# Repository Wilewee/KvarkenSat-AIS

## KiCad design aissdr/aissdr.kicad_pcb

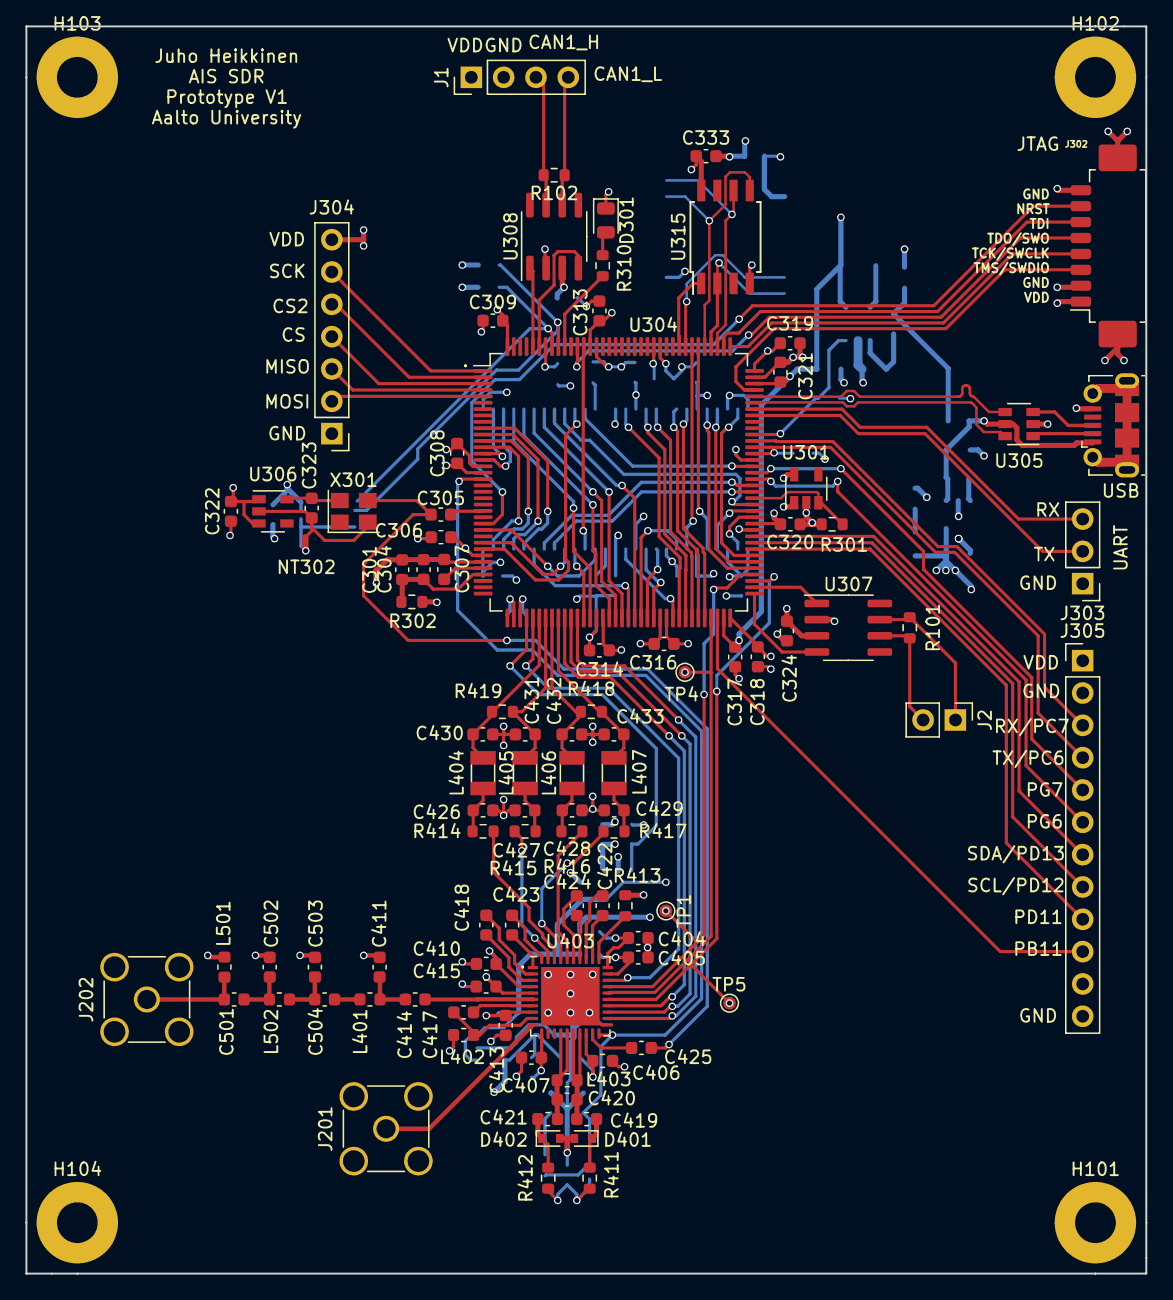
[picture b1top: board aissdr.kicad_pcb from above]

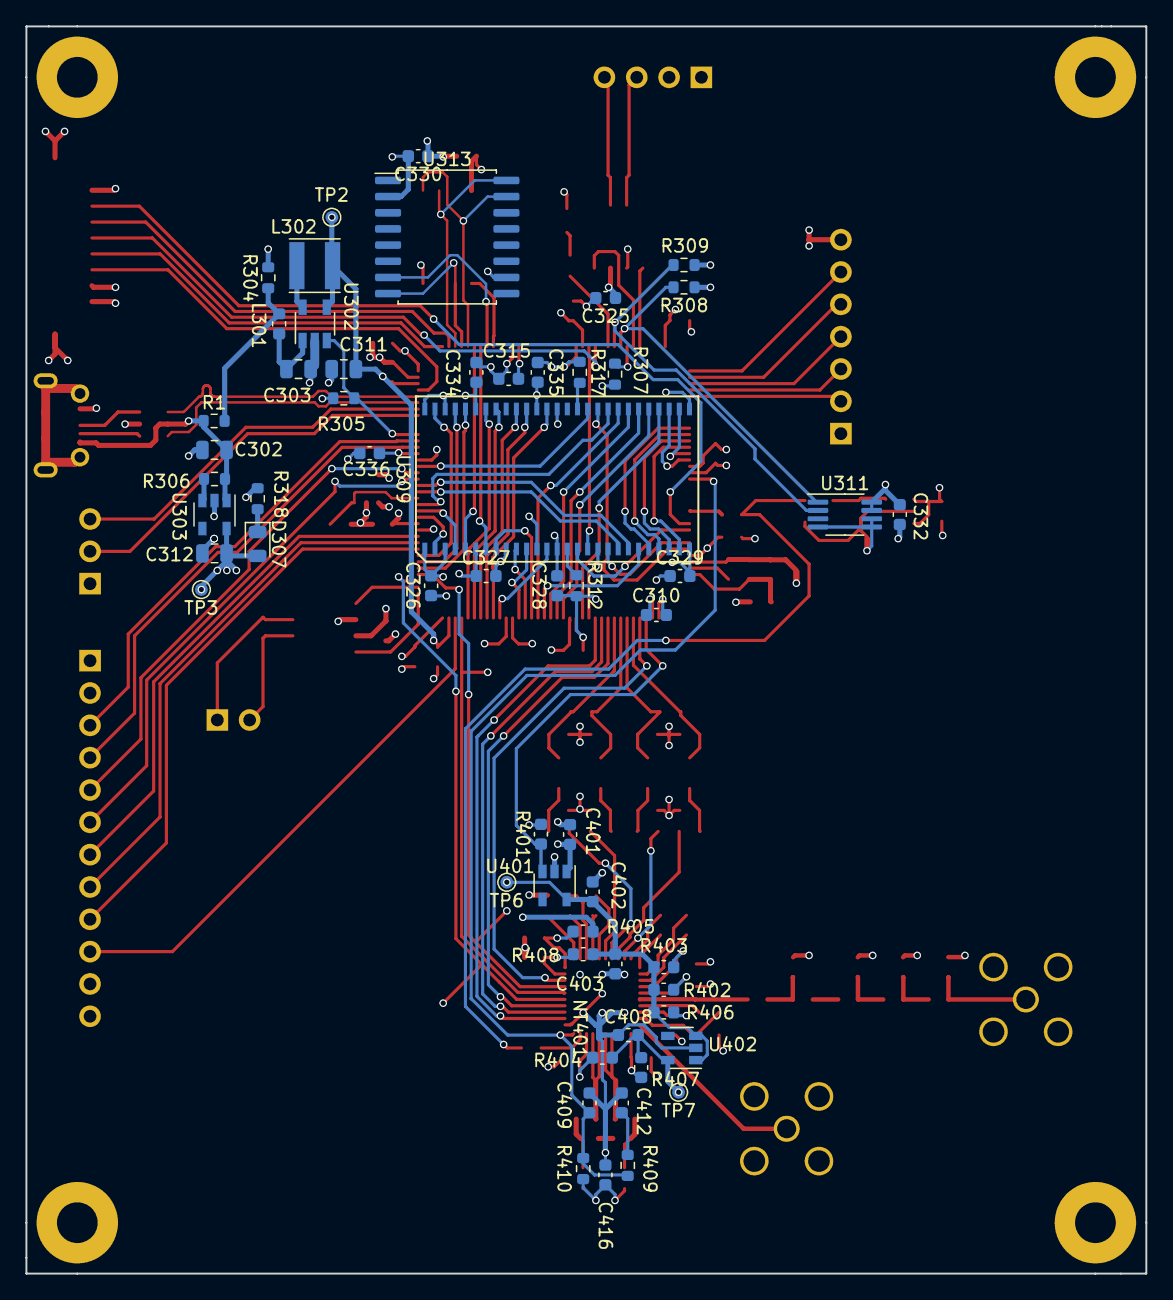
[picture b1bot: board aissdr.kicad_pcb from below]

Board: 4 copper layers, 88.0 x 98.0 mm, 160 parts (58 on the bottom side), 156 nets.

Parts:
C301, C307, C317, C321, C323, C402, C403, C408: 2u2; C_0603_1608Metric
C302: 2u2; C_0805_2012Metric
C303, C311, C312: 10u; C_0805_2012Metric
C304, C306, C308, C309, C310, C313, C314, C315, C316, C318, C319, C320, C322, C324, C325, C326, C327, C328, C329, C330, C332, C333, C334, C335, C336, C401, C404, C405: 100n; C_0603_1608Metric
C305, C414, C425: 1n; C_0603_1608Metric
C406, C407, C410, C413, C415: 10n; C_0603_1608Metric
C409, C412, C416: ?; C_0603_1608Metric
C411: 2p7; C_0603_1608Metric
C417: 18p; C_0603_1608Metric
C418, C422: 330p; C_0603_1608Metric
C419, C421: 47p; C_0603_1608Metric
C420: 0p; C_0603_1608Metric
C423, C424: 80p; C_0603_1608Metric
C426, C427, C428, C429, C430, C431, C432, C433: 3n3; C_0603_1608Metric
C501, C502: 10p; C_0603_1608Metric
C503: 12p; C_0603_1608Metric
C504: 100p; C_0603_1608Metric
D301: green; LED_0805_2012Metric
D307: red; LED_0805_2012Metric
D401, D402: SMV1234-079LF; D_SOD-523
H101, H102, H103, H104: MountingHole_Pad; MountingHole_3.2mm_M3_Pad
J1: Conn_01x07; PinHeader_1x04_P2.54mm_Vertical
J2: Conn_01x02; PinHeader_1x02_P2.54mm_Vertical
J201, J202: MCX right angle; SMA_Amphenol_901-144_Vertical
J301: USB_B_Micro; USB_Micro-B_Molex-105017-0001
J302: Molex_PicoBlade_53261-0871_1x08-1MP_P1.25mm_Horizontal
J303: PinHeader_1x03_P2.54mm_Vertical
J304: PinHeader_1x07_P2.54mm_Vertical
J305: PinHeader_1x12_P2.54mm_Vertical
L301: TBD; L_0603_1608Metric
L302: 2u2; L_Taiyo-Yuden_MD-4040
L401, L402: 150n; L_0603_1608Metric
L403: PCB inductor; L_0603_1608Metric
L404, L405, L406, L407: 470u; L_1007_2518Metric
L501: 27n; L_0603_1608Metric
L502: 15n; L_0603_1608Metric
NT301: VSSA; NetTie-2_SMD_Pad0.5mm
NT302: GNDXO; NetTie-2_SMD_Pad0.5mm
NT401: Net-Tie_2; NetTie-2_SMD_Pad0.5mm
R1, R304, R312, R317: 0; R_0603_1608Metric
R101, R102, R310, R318, R418, R419: 1k; R_0603_1608Metric
R301, R305, R306, R307: 470k; R_0603_1608Metric
R302: 10; R_0603_1608Metric
R308, R309, R411, R412, R413: 10k; R_0603_1608Metric
R401: 470k; C_0603_1608Metric
R402, R403, R406, R407: 3.3; C_0603_1608Metric
R404, R405, R408: 10; C_0603_1608Metric
R409, R410: ?; R_0603_1608Metric
R414, R415, R416, R417: 180; R_0603_1608Metric
TP1, TP2, TP3, TP4, TP5, TP6, TP7: TestPoint; TestPoint_Pad_D1.0mm
U301: MIC2091; SOT-23-5
U302: TPS62242-Q1; TSOT-23-5
U303: LP5907QMFX-3.3Q1; SOT-23-5
U304: STM32H743ZI; LQFP-144_20x20mm_P0.5mm
U305: USBLC6-2SC6; SOT-23-6
U306: LP5907MFX-3.0Q1; SOT-23-5
U307, U308: TCAN334; SOIC-8_3.9x4.9mm_P1.27mm
U309: IS42VS16160J-75TLI; TSOP-54-II
U311: AT30TS74; MSOP-8_3x3mm_P0.65mm
U313: MT29F1G01A; SOIC-16W_7.5x10.3mm_P1.27mm
U315: CY15B104QSN; SOIJ-8_5.3x5.3mm_P1.27mm
U401: LP5907QMFX-3.0Q1; SOT-23-5
U402: LP5907QMFX-2.8Q1; SOT-23-5
U403: CMX994A; QFN-40-1EP_6x6mm_P0.5mm_EP4.6x4.6mm
X301: ECS-TXO-2520-33-100-AN-TR; Crystal_SMD_3225-4Pin_3.2x2.5mm

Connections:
/3V3_PL: C306.2, C308.2, C309.2, C310.2, C312.1, C313.2, C314.2, C315.2, C316.2, C318.2, C319.2, C320.2, C322.2, C324.1, C325.1, C330.2, C332.2, C333.1, C336.2, C401.1, D307.2, J1.1, J302.1, J304.7, J305.1, R302.2, R304.2, R308.1, R309.1, R405.2, TP3.1, U301.1, U303.5, U304.17, U304.30, U304.39, U304.52, U304.62, U304.72, U304.84, U304.95, U304.108, U304.121, U304.131, U304.144, U306.1, U306.3, U307.3, U308.3, U311.7, U311.8, U313.2, U315.8, U401.1
/CAN1_H: J1.3, R102.2, U308.7
/CAN1_L: J1.4, R102.1, U308.6
/CAN2_H: J2.1, R101.2, U307.7
/CAN2_L: J2.2, R101.1, U307.6
/Transceiver/Filter/RF_Antenna: C501.2, J202.1, L501.1
/Transceiver/Filter/RF_RX: C504.1, L401.1
/Transceiver/Microcontroller/5V_USB: C302.1, J301.1, R1.1, R306.1, U303.1, U305.5
/Transceiver/Microcontroller/ADC_I_N: C431.2, L405.2, R419.1, U304.43
/Transceiver/Microcontroller/ADC_I_P: C430.1, L404.2, R419.2, U304.42
/Transceiver/Microcontroller/ADC_Q_N: C433.2, L407.2, R418.1, U304.45
/Transceiver/Microcontroller/ADC_Q_P: C432.1, L406.2, R418.2, U304.44
/Transceiver/Microcontroller/BOOT0: R307.2, U304.138
/Transceiver/Microcontroller/DEMOD_RESET: U304.41, U403.28
/Transceiver/Microcontroller/DEMOD_RXEN: U304.47, U403.23
/Transceiver/Microcontroller/DEMOD_TXEN: U304.48, U403.22
/Transceiver/Microcontroller/EN_3V0_A: R401.1, U304.40, U401.3
/Transceiver/Microcontroller/EN_3V3_D: R306.2, U303.3
/Transceiver/Microcontroller/EN_RAM: R301.1, U301.3, U304.88
/Transceiver/Microcontroller/EN_VDDCORE: R305.1, U302.3, U304.98
/Transceiver/Microcontroller/FDCAN1_RX: U304.139, U308.4
/Transceiver/Microcontroller/FDCAN1_TX: U304.140, U308.1
/Transceiver/Microcontroller/FDCAN2_RX: U304.73, U307.4
/Transceiver/Microcontroller/FDCAN2_TX: U304.74, U307.1
/Transceiver/Microcontroller/FLASH_CS: U304.116, U313.7
/Transceiver/Microcontroller/FMC_A0: U304.10, U309.23
/Transceiver/Microcontroller/FMC_A1: U304.11, U309.24
/Transceiver/Microcontroller/FMC_A2: U304.12, U309.25
/Transceiver/Microcontroller/FMC_A3: U304.13, U309.26
/Transceiver/Microcontroller/FMC_A4: U304.14, U309.29
/Transceiver/Microcontroller/FMC_A5: U304.15, U309.30
/Transceiver/Microcontroller/FMC_A6: U304.50, U309.31
/Transceiver/Microcontroller/FMC_A7: U304.53, U309.32
/Transceiver/Microcontroller/FMC_A8: U304.54, U309.33
/Transceiver/Microcontroller/FMC_A9: U304.55, U309.34
/Transceiver/Microcontroller/FMC_A10: U304.56, U309.22
/Transceiver/Microcontroller/FMC_A11: U304.57, U309.35
/Transceiver/Microcontroller/FMC_A12: U304.87, U309.36
/Transceiver/Microcontroller/FMC_BA0: U304.89, U309.20
/Transceiver/Microcontroller/FMC_BA1: U304.90, U309.21
/Transceiver/Microcontroller/FMC_D0: U304.85, U309.2
/Transceiver/Microcontroller/FMC_D1: U304.86, U309.4
/Transceiver/Microcontroller/FMC_D2: U304.114, U309.5
/Transceiver/Microcontroller/FMC_D3: U304.115, U309.7
/Transceiver/Microcontroller/FMC_D4: U304.58, U309.8
/Transceiver/Microcontroller/FMC_D5: U304.59, U309.10
/Transceiver/Microcontroller/FMC_D6: U304.60, U309.11
/Transceiver/Microcontroller/FMC_D7: U304.63, U309.13
/Transceiver/Microcontroller/FMC_D8: U304.64, U309.42
/Transceiver/Microcontroller/FMC_D9: U304.65, U309.44
/Transceiver/Microcontroller/FMC_D10: U304.66, U309.45
/Transceiver/Microcontroller/FMC_D11: U304.67, U309.47
/Transceiver/Microcontroller/FMC_D12: U304.68, U309.48
/Transceiver/Microcontroller/FMC_D13: U304.77, U309.50
/Transceiver/Microcontroller/FMC_D14: U304.78, U309.51
/Transceiver/Microcontroller/FMC_D15: U304.79, U309.53
/Transceiver/Microcontroller/FMC_SDCKE0: U304.29, U309.37
/Transceiver/Microcontroller/FMC_SDCLK: U304.93, U309.38
/Transceiver/Microcontroller/FMC_SDNCAS: U304.132, U309.17
/Transceiver/Microcontroller/FMC_SDNE0: U304.28, U309.19
/Transceiver/Microcontroller/FMC_SDNRAS: U304.49, U309.18
/Transceiver/Microcontroller/FMC_SDNWE: U304.26, U309.16
/Transceiver/Microcontroller/FRAM_CS: U304.117, U315.1
/Transceiver/Microcontroller/FREF: C305.2, C425.1, X301.3
/Transceiver/Microcontroller/FREF_MCU: C305.1, U304.23
/Transceiver/Microcontroller/GNDXO: C323.1, NT302.1, U306.2, X301.2
/Transceiver/Microcontroller/I2C1_SCL: R309.2, U304.136, U311.2
/Transceiver/Microcontroller/I2C1_SDA: R308.2, U304.137, U311.1
/Transceiver/Microcontroller/I2C4_SCL: J305.8, U304.81
/Transceiver/Microcontroller/I2C4_SDA: J305.7, U304.82
/Transceiver/Microcontroller/JTCK_SWCLK: J302.4, U304.109
/Transceiver/Microcontroller/JTDI: J302.6, U304.110
/Transceiver/Microcontroller/JTDO_SWO: J302.5, U304.133
/Transceiver/Microcontroller/JTMS_SWDIO: J302.3, U304.105
/Transceiver/Microcontroller/LED1: R310.1, U304.135
/Transceiver/Microcontroller/NRST: J302.7, U304.25
/Transceiver/Microcontroller/PB11: J305.10, U304.70
/Transceiver/Microcontroller/PD11: J305.9, U304.80
/Transceiver/Microcontroller/PG6: J305.6, U304.91
/Transceiver/Microcontroller/PG7: J305.5, U304.92
/Transceiver/Microcontroller/R_SCK: TP4.1, U304.69, U403.26
/Transceiver/Microcontroller/SPI3_MISO: U304.112, U313.8, U315.2
/Transceiver/Microcontroller/SPI3_MOSI: U304.113, U313.15, U315.5
/Transceiver/Microcontroller/SPI3_SCK: U304.111, U313.16, U315.6
/Transceiver/Microcontroller/SPI4_CS: J304.4, U304.3
/Transceiver/Microcontroller/SPI4_CS2: J304.5, U304.2
/Transceiver/Microcontroller/SPI4_MISO: J304.3, U304.4
/Transceiver/Microcontroller/SPI4_MOSI: J304.2, U304.5
/Transceiver/Microcontroller/SPI4_SCK: J304.6, U304.1
/Transceiver/Microcontroller/USART1_RX: J303.3, U304.102
/Transceiver/Microcontroller/USART1_TX: J303.2, U304.101
/Transceiver/Microcontroller/USART6_RX: J305.3, U304.97
/Transceiver/Microcontroller/USART6_TX: J305.4, U304.96
/Transceiver/Microcontroller/USB_CONN_D+: J301.3, U305.3
/Transceiver/Microcontroller/USB_CONN_D-: J301.2, U305.1
/Transceiver/Microcontroller/USB_D+: U304.104, U305.4
/Transceiver/Microcontroller/USB_D-: U304.103, U305.6
/Transceiver/Microcontroller/VCO_CV: C409.2, R409.1, R410.1, U304.18, U403.20
/Transceiver/Microcontroller/VDDA: C301.2, C304.2, R302.1, U304.33
/Transceiver/Microcontroller/VDDCORE: C311.1, C317.1, C321.2, L302.1, TP2.1, U302.4, U304.71, U304.106
/Transceiver/Microcontroller/VDDRAM: C326.2, C327.2, C328.2, C329.2, C334.2, C335.2, U301.5, U309.1, U309.3, U309.9, U309.14, U309.27, U309.43, U309.49
/Transceiver/Microcontroller/VDDXO: C323.2, U306.5, X301.4
/Transceiver/Microcontroller/VREF+: C307.2, U304.32
/Transceiver/Microcontroller/VSSA: C301.1, C304.1, C307.1, NT301.1, U304.31
/Transceiver/Receiver/3V0_A: C402.1, C403.2, R402.2, R403.2, R406.2, R408.2, TP6.1, U401.5, U402.1, U402.3
/Transceiver/Receiver/CDATA: TP1.1, U304.76, U403.27
/Transceiver/Receiver/CMX_RXIN: R415.2, U403.39
/Transceiver/Receiver/CMX_RXIP: R414.2, U403.38
/Transceiver/Receiver/CMX_RXQN: R417.2, U403.37
/Transceiver/Receiver/CMX_RXQP: R416.2, U403.36
/Transceiver/Receiver/CSN: U304.46, U403.24
/Transceiver/Receiver/GNDOSC: C408.1, C409.1, C412.1, C416.1, D401.2, D402.2, NT401.1, U402.2
/Transceiver/Receiver/RDATA: TP5.1, U304.75, U403.25
/Transceiver/Receiver/RF_TXLO: J201.1, U403.10
/Transceiver/Receiver/VDDOSC: C408.2, R404.2, R407.2, TP7.1, U402.5
GND: C302.2, C303.2, C306.1, C308.1, C309.1, C310.1, C311.2, C312.2, C313.1, C314.1, C315.1, C316.1, C317.2, C318.1, C319.1, C320.1, C321.1, C322.1, C324.2, C325.2, C326.1, C327.1, C328.1, C329.1, C330.1, C332.1, C333.2, C334.1, C335.1, C336.1, C401.2, C402.2, C403.1, C404.1, C405.1, C406.1, C407.1, C410.1, C411.1, C413.1, C415.1, C426.2, C427.1, C428.2, C429.1, C430.2, C431.1, C432.2, C433.1, C502.1, C503.1, D301.1, J1.2, J201.2, J202.2, J301.5, J302.2, J302.8, J302.MP, J303.1, J304.1, J305.2, J305.12, L402.1, L501.2, NT301.2, NT302.2, NT401.2, R301.2, R305.2, R307.1, R312.2, R317.1, R318.2, R401.2, R413.1, U301.2, U302.2, U303.2, U304.16, U304.38, U304.51, U304.61, U304.83, U304.94, U304.107, U304.120, U304.130, U305.2, U307.2, U308.2, U309.6, U309.12, U309.28, U309.41, U309.46, U309.52, U309.54, U311.4, U311.5, U311.6, U313.10, U315.4, U401.2, U403.21, U403.41
unnamed: C303.1, L301.2, U302.1
unnamed: C404.2, R405.1, U403.30
unnamed: C405.2, R408.1, U403.29
unnamed: C406.2, R404.1, U403.18
unnamed: C407.2, R407.1, U403.11
unnamed: C410.2, R403.1, U403.4
unnamed: C411.2, C414.2, L401.2
unnamed: C412.2, R409.2
unnamed: C413.2, R406.1, U403.8
unnamed: C414.1, U403.6
unnamed: C415.2, R402.1, U403.5
unnamed: C416.2, R410.2, R411.1, R412.1
unnamed: C417.1, L402.2, U403.9
unnamed: C417.2, U403.7
unnamed: C418.1, U403.3
unnamed: C418.2, U403.2
unnamed: C419.1, D401.1, R411.2
unnamed: C419.2, C420.2, L403.2, U403.16, U403.17
unnamed: C420.1, C421.2, L403.1, U403.14, U403.15
unnamed: C421.1, D402.1, R412.2
unnamed: C422.1, U403.32
unnamed: C422.2, U403.33
unnamed: C423.1, U403.1
unnamed: C423.2, U403.40
unnamed: C424.1, U403.34
unnamed: C424.2, U403.35
unnamed: C425.2, U403.19
unnamed: C426.1, L404.1, R414.1
unnamed: C427.2, L405.1, R415.1
unnamed: C428.1, L406.1, R416.1
unnamed: C429.2, L407.1, R417.1
unnamed: C501.1, C502.2, L502.2
unnamed: C503.2, C504.2, L502.1
unnamed: D301.2, R310.2
unnamed: D307.1, R318.1
unnamed: L301.1, R1.2, R304.1
unnamed: L302.2, U302.5
unnamed: R312.1, U309.15
unnamed: R317.2, U309.39
unnamed: R413.2, U403.31

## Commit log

2021-11-30 Added KiCad design files
    Added KiCad files. This version of the PCB has some design errors, but is mostly representative of the current design
